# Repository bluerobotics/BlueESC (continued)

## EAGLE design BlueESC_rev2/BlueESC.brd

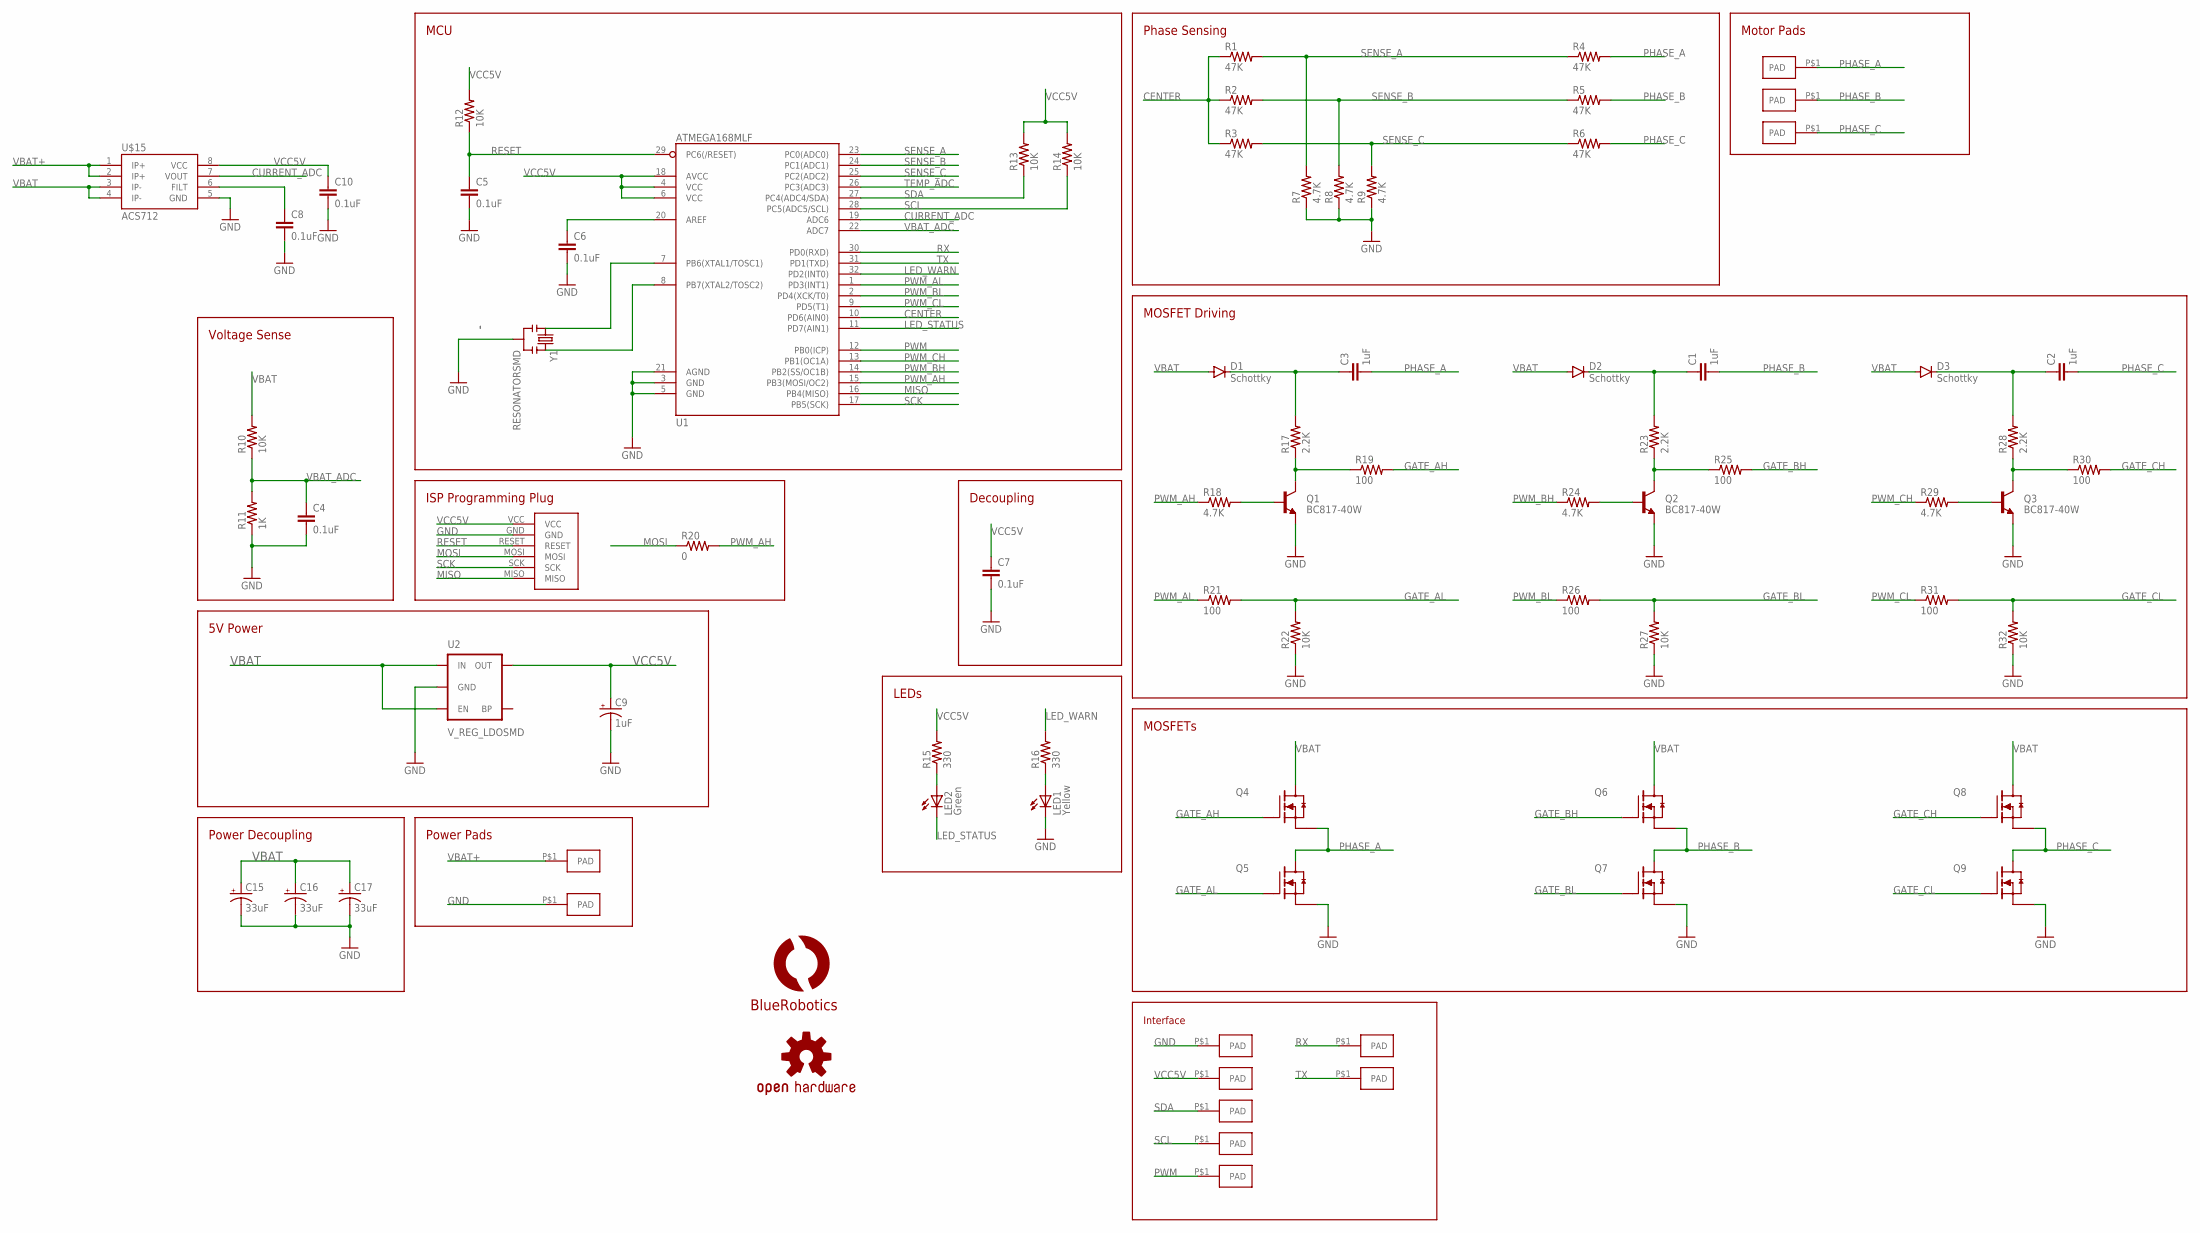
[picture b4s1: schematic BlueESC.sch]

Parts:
C1, C2, C3: 1uF; 0805
C4, C5, C6, C7, C8, C10: 0.1uF; 0603-CAP
C9: 1uF; EIA3216
C15, C16, C17: 33uF; EIA6032
D1, D2, D3: Schottky; SOD-323
LED1: Yellow; LED3MM-NS
LED2: Green; LED3MM-NS
LOGO1: OSHW-LOGOS; OSHW-LOGO-S
Q1, Q2, Q3: BC817-40W; SOT23
Q4, Q5, Q6, Q7, Q8, Q9: SI7370; POWERPAK-SO-08
R1, R2, R3, R4, R5, R6: 47K; 0603-RES
R7, R8, R9, R18, R24, R29: 4.7K; 0603-RES
R10, R12, R13, R14, R22, R27, R32: 10K; 0603-RES
R11: 1K; 0603-RES
R15, R16: 330; 0603-RES
R17, R23, R28: 2.2K; 0603-RES
R19, R21, R25, R26, R30, R31: 100; 0603-RES
R20: 0; 0603-RES
U1: ATMEGA168MLF; MLF32
U2: V_REG_LDOSMD; SOT23-5
U$1, U$2, U$5, U$6, U$7: PAD2X3MM; PAD-2X3MM
U$3, U$8, U$9, U$10, U$11, U$12, U$13: PAD1.5X3MM; PAD-1.5X3MM
U$4: LOGOBR-LOGO-S; BR-LOGO-SMALL
U$14: AVR-ISPTINY-SMD; AVR-ISP-TINY
U$15: ACS712; SO08
Y1: RESONATORSMD; RESONATOR-SMD

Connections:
CENTER: R1.1, R2.1, R3.1, U1.10 (PD6(AIN0))
CURRENT_ADC: U1.19 (ADC6), U$15.7 (VOUT)
GATE_AH: Q4.4 (G), R19.2
GATE_AL: Q5.4 (G), R21.2, R22.2
GATE_BH: Q6.4 (G), R25.2
GATE_BL: Q7.4 (G), R26.2, R27.2
GATE_CH: Q8.4 (G), R30.2
GATE_CL: Q9.4 (G), R31.2, R32.2
GND: C4.2, C5.2, C6.2, C7.2, C8.2, C9.C (-), C10.2, C15.P$2 (-), C16.P$2 (-), C17.P$2 (-), LED1.K (C), Q1.2 (E), Q2.2 (E), Q3.2 (E), Q5.3 (S3), Q7.3 (S3), Q9.3 (S3), R7.1, R8.1, R9.1, R11.1, R22.1, R27.1, R32.1, U1.3 (GND), U1.5 (GND), U1.21 (AGND), U2.2 (GND), U$2.P$1, U$3.P$1, U$14.GND, U$15.5 (GND), Y1.2
LED_STATUS: LED2.K (C), U1.11 (PD7(AIN1))
LED_WARN: R16.2, U1.32 (PD2(INT0))
MISO: U1.16 (PB4(MISO)), U$14.MISO
unnamed: C8.1, U$15.6 (FILT)
unnamed: Q1.1 (B), R18.2
unnamed: LED1.A, R16.1
unnamed: Q1.3 (C), R17.1, R19.1
unnamed: Q2.1 (B), R24.2
unnamed: Q2.3 (C), R23.1, R25.1
unnamed: Q3.1 (B), R29.2
unnamed: C6.1, U1.20 (AREF)
unnamed: Q3.3 (C), R28.1, R30.1
unnamed: U1.7 (PB6(XTAL1/TOSC1)), Y1.1
unnamed: U1.8 (PB7(XTAL2/TOSC2)), Y1.3
unnamed: C3.1, D1.C, R17.2
unnamed: C1.1, D2.C, R23.2
unnamed: LED2.A, R15.1
unnamed: C2.1, D3.C, R28.2
PHASE_A: C3.2, Q4.3 (S3), Q5.5-8 (D), R4.2, U$5.P$1
PHASE_B: C1.2, Q6.3 (S3), Q7.5-8 (D), R5.2, U$6.P$1
PHASE_C: C2.2, Q8.3 (S3), Q9.5-8 (D), R6.2, U$7.P$1
PWM: U1.12 (PB0(ICP)), U$11.P$1
PWM_AL: R21.1, U1.1 (PD3(INT1))
PWM_BH: R24.1, U1.14 (PB2(SS/OC1B))
PWM_BL: R26.1, U1.2 (PD4(XCK/T0))
PWM_CH: R29.1, U1.13 (PB1(OC1A))
PWM_CL: R31.1, U1.9 (PD5(T1))
RESET: C5.1, R12.1, U1.29 (PC6(/RESET)), U$14.RESET
RX: U1.30 (PD0(RXD)), U$12.P$1
SCK: U1.17 (PB5(SCK)), U$14.SCK
SCL: R14.1, U1.28 (PC5(ADC5/SCL)), U$10.P$1
SDA: R13.1, U1.27 (PC4(ADC4/SDA)), U$9.P$1
SENSE_A: R1.2, R4.1, R7.2, U1.23 (PC0(ADC0))
SENSE_B: R2.2, R5.1, R8.2, U1.24 (PC1(ADC1))
SENSE_C: R3.2, R6.1, R9.2, U1.25 (PC2(ADC2))
TEMP_ADC: U1.26 (PC3(ADC3))
TX: U1.31 (PD1(TXD)), U$13.P$1
VBAT: C15.P$1 (+), C16.P$1 (+), C17.P$1 (+), D1.A, D2.A, D3.A, Q4.5-8 (D), Q6.5-8 (D), Q8.5-8 (D), R10.2, U2.1 (IN), U2.3 (EN), U$15.3 (IP-), U$15.4 (IP-)
VBAT+: U$1.P$1, U$15.1 (IP+), U$15.2 (IP+)
VBAT_ADC: C4.1, R10.1, R11.2, U1.22 (ADC7)
VCC5V: C7.1, C9.A (+), C10.1, R12.2, R13.2, R14.2, R15.2, U1.4 (VCC), U1.6 (VCC), U1.18 (AVCC), U2.5 (OUT), U$8.P$1, U$14.VCC, U$15.8 (VCC)

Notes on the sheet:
MOSFET Driving
MOSFETs
MCU
Decoupling
LEDs
Phase Sensing
ISP Programming Plug
Voltage Sense
5V Power
Power Decoupling
Power Pads
Motor Pads
Interface

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
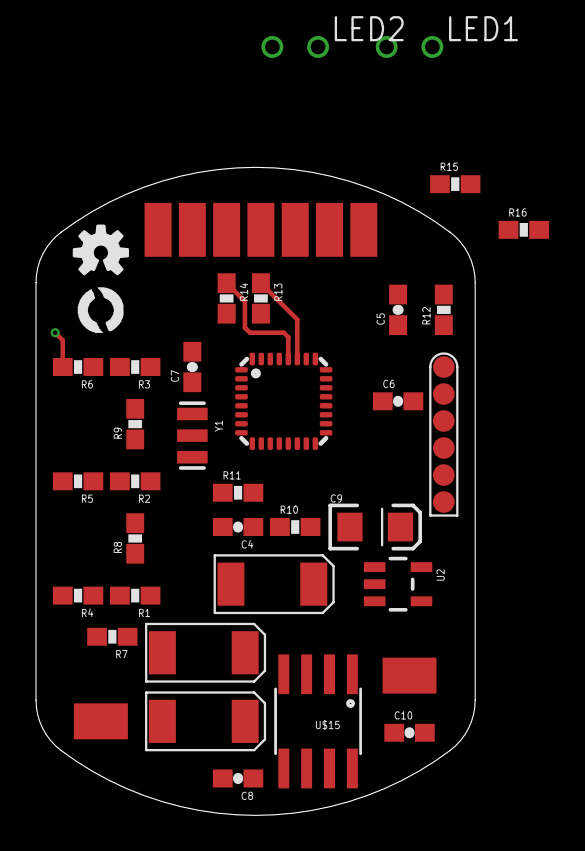
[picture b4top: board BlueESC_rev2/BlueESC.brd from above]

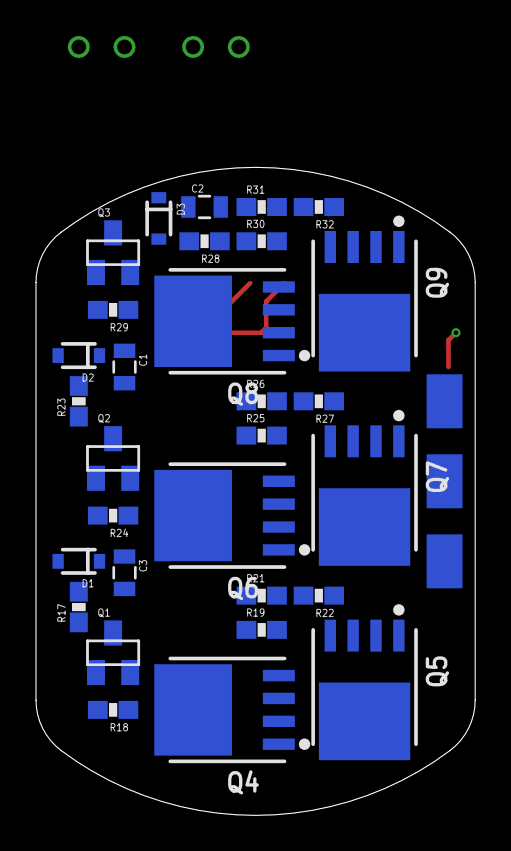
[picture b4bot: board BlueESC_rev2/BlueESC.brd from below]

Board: 4 copper layers, 24.4 x 36.0 mm, 77 parts (33 on the bottom side), 50 nets.

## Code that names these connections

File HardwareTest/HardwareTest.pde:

#include <WProgram.h>

#define CURRENT_ADC A3
#define VBAT_ADC A6
#define TEMP_ADC A7

#define BLUE_LED 10
#define RED_LED 9

//#define BLINK_CURRENT
#define BLINK_VBAT
//#define BLINK_TEMP

void blinkBlue() {
  digitalWrite(BLUE_LED,LOW);
  delay(50);
  digitalWrite(BLUE_LED,HIGH);
  delay(300);
}

void blinkRed() {
  digitalWrite(RED_LED,HIGH);
  delay(50);
  digitalWrite(RED_LED,LOW);
  delay(300);
}

void wait() {
  delay(1000);
}

void blink() {
  int16_t value;
#ifdef BLINK_CURRENT
  value = analogRead(CURRENT_ADC);
#endif
#ifdef BLINK_VBAT
  value = analogRead(VBAT_ADC);
#endif
#ifdef BLINK_TEMP
  value = analogRead(TEMP_ADC);
#endif

  uint8_t hundreds = value/100;
  uint8_t tens = (value%100)/10;
  uint8_t units = value%10;

  for ( uint8_t i = 0 ; i < hundreds ; i++ ) {
    blinkBlue();
  }
  wait();
  for ( uint8_t i = 0 ; i < tens ; i++ ) {
    blinkRed();
  }
  wait();
  for ( uint8_t i = 0 ; i < units ; i++ ) {
    blinkBlue();
  }
}

void setup() {
  Serial.begin(9600);

  pinMode(CURRENT_ADC,INPUT);
  pinMode(VBAT_ADC,INPUT);
  pinMode(TEMP_ADC,INPUT);

  pinMode(BLUE_LED,OUTPUT);
  pinMode(RED_LED,OUTPUT);
  digitalWrite(BLUE_LED,HIGH);

  blinkBlue();
  blinkRed();
  blinkBlue();

  delay(2000);
}

void loop() {
  Serial.print(analogRead(CURRENT_ADC));Serial.print(" ");
  Serial.print(analogRead(VBAT_ADC));Serial.print(" ");
  Serial.print(analogRead(TEMP_ADC));Serial.println("");

  blink();

  delay(2000);
}

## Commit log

2014-08-26 Initial commit of rev1 schematic and board layout. They have been successfully tested.
2014-08-26 Update README.md
    Added basic readme.
2014-08-26 Update README.md
    Add mosfet type to readme.
2014-08-27 Update README.md
    Minor changes to readme.
2014-08-27 Removed misleading label from MOSFETS on board layout.
2014-08-27 Update README.md
    Enabled safemode in upload commands in readme.
2014-08-27 Update README.md
    Updated current ratings.
2014-08-28 Added photos of the BlueESC rev 1 prototype.
2014-08-28 Update README.md
    Added image to readme.
2014-08-28 Update README.md
    Fixed image.
2014-08-28 Update README.md
    Added thumbnail to youtube video.
2014-08-30 Added diodes and capacitors near fets. Need to verify necessary package sizes.
2014-09-02 Small changes.
2014-09-03 Changed value of charge pump capacitors because there are more package sizes available for 1.0uF.
2014-09-03 Removed sense filtering capacitors and changed voltage divider resistor values.
2014-09-03 Updated schematic to reflect changes made to rev1a prototype. This includes different passive values and the addition of charge pumps for the n-channel fets.
2014-09-03 Placed more components on board layout.
2014-09-04 Update README.md
    Add Mac compilation instructions.
2014-09-19 Small changes before testing of rev1a.
2014-09-22 Added ACS71X to the schematic and board layout to measure current.
2014-09-30 Updated rev3 schematic and split the schematic into two boards.
2014-10-01 Rev3 (two boards) laid out and ready to go. Final review may create a few changes.
2014-10-07 Rev 3 changes. Boards have been ordered.
2014-10-07 Minor changes to README for rev3.
2014-10-19 Removed rev 2 files. This version was a 4-layer board that was never completed.
2014-11-04 Update README.md
    Minor updates to readme.
2014-11-04 Update README.md
    Minor readme updates.
2014-11-04 I2C updates to readme.
2014-11-04 Added revision 4 files. No major changes yet except for decoupling capacitor values.
2014-11-04 Updated readme and added image of rev3.
2014-12-11 Enlarged wire holes for 16AWG.
2014-12-26 Commit before major changes to rev 4
2015-01-08 Major updates on revision 4 include rearranged components, removal of programming pins, and new board shapes.
2015-01-28 Update README.md
    Minor update.
2015-02-16 Minor changes before ordering production boards.
2015-05-29 Updated I2C protocol to the actual protocol that will be used.
2015-05-29 Updated the speed command I2C.
2015-06-21 Added rev 5 board and schematic files.
2015-06-21 Removed old revisions.
2015-06-21 Moved current revision to a new folder.
2015-06-21 Added hardware test files to branch.
2015-06-21 Added BlueESC Basic files. This is by no means complete. Work in pgrgress.
2015-06-21 Added BlueESC Basic with FET drivers.
2015-06-21 Added programmer schematic.
2015-06-21 Added git ignore file.
2015-06-21 Updated README and notes.
2015-06-21 Added version release note.
2015-06-21 Added videos to readme.
2015-06-21 Added even more to readme.
2015-06-21 Added link to Arduino library.
2015-07-06 Added new image.
2015-08-12 Switch to SMT LEDs.
2015-08-12 Added PWM pull-down resistor.
2015-08-16 New logic board prototype ordered 8/14/15.
2015-09-24 Updated PWM pull down to 470K to avoid avoid beating out the internal pull-ups used in ArduinoUSBLinker.
2015-11-01 Update README.md
    Fixed typos.
2015-11-01 Fixed a few more typos.
2015-11-02 Minor updates to readme.
2015-11-02 Combined logic and power boards into a single board. This is done for several reasons. The first is to create a consistent single schematic to help others view the design. The second is for manufactu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
2015-11-02 Reorganized combined schematic and broke everything into multiple sheets for easier viewing.
2015-11-02 Put R20 on back of power board to minimize soldering errors.
2015-11-02 Updated MOSFET footprint to TDSON-8 to accommodate new FET and to fix potential soldering errors. This should still fit the SiR158DP as well.
2015-11-02 Updated schematic sheets to use the new BR frame.
2015-11-02 Added pdf version of schematic for convenience.
2015-11-02 Added link to pdf schematic in the README.
2015-11-05 Minor updates and reference marking for Vscore.
2015-12-08 Removed a ground via that was too close to a solder point.
